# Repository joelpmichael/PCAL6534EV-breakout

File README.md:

# PCAL6534EV Breakout

## Contents

- [What?](#what)
- [Why?](#why)
- [How?](#how)
- [Can I buy one?](#can-i-buy-one)
- [Can I make one?](#can-i-make-one)
- [Can I make heaps and sell them?](#can-i-make-heaps-and-sell-them)
- [No really, why?](#no-really-why)
- [Board revision history](#board-revision-history)

## What?

This is a breakout board for the [NXP PCAL6534EV I2C GPIO expander](https://www.nxp.com/products/interfaces/ic-spi-i3c-interface-devices/general-purpose-i-o-gpio/ultra-low-voltage-level-translating-34-bit-ic-bus-smbus-i-o-expander:PCAL6534). The board breaks out 32 out of the possible 34 GPIO pins, with 26 of the 32 GPIO pins arranged in a DIP-style layout at 12.7mm column spacing which is perfect for breadboard or protoboard use. There is also a [SparkFun QWIIC-compatible connector](https://www.sparkfun.com/qwiic), for easy connection to other QWIIC-compatible boards.

## Why?

It all started a few years ago, when I was on a holiday in Italy and I found this wonderful little cafe that I stopped at for lunch. I convinced the chef to give me his secret recipe, which he did on one condition: I'm not allowed to tell anybody else until the day I die.

I'm still well and truly alive despite all reports to the contrary, and despite the lack of sleep (#DadLife), so I'm not going to tell you, instead I'm going to make this breakout board instead.

## How?

Please refer to the [PCAL6534EV Datasheet](https://www.nxp.com/docs/en/data-sheet/PCAL6534.pdf) and the [Board Schematic](PCAL6534EV-breakout.pdf) for further details.

- [Connecting](#connecting)
- [Powering](#powering)
- [I2C communication](#i2c-communication)
- [Interrupt and reset](#interrupt-and-reset)
- [GPIO use](#gpio-use)
- [Mounting](#mounting)

### Connecting

Solder the 20-pin headers into each side and slam it into a breadboard! The width is minimised to allow access to 3 pins on each side - wider breakout and prototype boards have always annoyed me by only allowing access to 1 or 2 pins on each side.

Use the QWIIC-compatible connector J1 to connect to your MCU, as the PCAL6534EV is optimised to run at 3.3V. You may run into current supply limits when using the very thin 28AWG wire in QWIIC-compatible cables, as the PCAL6534EV can source up to 450mA or sink up to 500mA of current. If you're driving a lot of LEDs or something, hook up an additional 3.3V power connection to the pin header, and maybe a chonky electrolytic capacitor across 3V3 or VIO.

You can also solder wires directly to the pin headers if needed, or solder the pin headers to a protoboard, or just do what you want I'm not your mum.

At the very bottom edge of the breakout board is an exposed ground plane, designed for you to attach an alligator clip while probing with a multimeter, osciloscope, or logic analyzer.

### Powering

The PCAL6534EV requires 2 power supplies, VDD(i2c) and VDD(p). VDD(i2c) is wired to the 3V3 rail, and must be in the range of 0.8 to 3.6V, allowing you to use lower voltage MCU or FPGA I2C lines. VDD(p) is wired to jumper JP1, and must be in the range of 1.65 to 5.5V. Jumper JP1 selects the source rail of VDD(p), either 3V3 or VIO. When jumper JP1 is set to 3V3, the 3V3 input voltage range is narrowed to 1.65 to 3.6V. When jumper JP1 is set to VIO, the desired IO voltage must be supplied on the VIO pin.

### I2C communication

The PCAL6534EV supports I2C standard-mode at up to 100kHz, fast-mode at up to 400kHz, or fast-mode plus at up to 1000kHz. The breakout board contains 4.7kΩ pull-up resistors from I2C SDA and SCL lines to the 3V3 rail. These pull-up resistors can be disabled by cutting the PCB trace jumper JP4 on the back of the breakout board.

The PCAL6534EV I2C device address is set by connecting the ADDR line to either SDA, SCL, VSS (ground), or VDD(i2c), with a base 7-bit I2C device address of `0b0100000` (`0x20`). The breakout board defaults to the base address `0x20`, and by cutting and bridging PCB jumper pins on JP2 and JP3 can set the device address to `0x20`, `0x21`, `0x22`, or `0x23` according to the following table:

|Jumper|Pins|Address|
|------|----|-------|
|JP2|1-2|0x20|
|JP2|2-3|0x21|
|JP3|1-2|0x22|
|JP3|2-3|0x23|

> ⚠️ SDA and SCL pins **ARE NOT** 5V-tolerant!

### Interrupt and reset

The PCAL6534EV contains both an Interrupt (IRQ) line, and a Reset (RST) line. Both lines are active-low. The IRQ output line uses an open-drain driver, and the breakout board contains a 10kΩ pull-up resistor to VDD(i2c) because most likely you'll be using the IRQ signal on the same MCU that the I2C controller is running on. If you really really really REALLY need to change this, you can remove R4 and connect another pull-up resistor between R4 pad 1 (closest to JP4) and VIO, ensuring that VIO is limited to 3.3V.

The Reset input line is an active-low input, and the breakout board contains a a 10kΩ pull-up resistor to VDD(i2c) because most likely you'll be supplying the Reset signal from the same MCU that the I2C controller is running on, or you've wired the Reset line to an external momentary switch and you don't care about the voltage. If you're using a momentary switch, add a 0.1µF capacitor in parallel to the switch for a hardware debouncer and noise filter. It is safe to leave the Reset line disconnected from the breakout board.

> ⚠️ Interrupt and Reset pins **ARE NOT** 5V-tolerant!

### GPIO use

It's a... uh... low-speed GPIO? Just use them, the default PCAL6534EV configuration should work for most cases! All the GPIO pins are 5V-tolerant, and will even produce 5V output if you're using 5V on VIO, so feel free to hook them up to your old MEGA328P-based Arduinos and do voltage level translation. You can even drive a LOT of LEDs directly from the GPIO pins - every pin is recommended to source 10mA or sink 25mA of current, with a combined total of 450mA of sourcing current and 500mA of sinking current.

For advanced use-cases, such as enabling internal 100kΩ pull-up or pull-down resistors, switching between push-pull or open-drain output mode, enabling interrupt generation, enabling debouncing filters, or reducing the drive strength to limit GPIO switching noise, please refer to the datasheet and the example source code.

> ✔️ GPIO pins **ARE** 5V-tolerant!

### Mounting

Due to asthetics and space constraints there isn't enough room for a full-size mounting hole, however in the middle of the OSHW logo there is a 1mm pilot hole that you can use to drill a mounting hole. Ideal? No. Pragmatic? Yes. 

Personally I wouldn't drill a hole larger than 3mm, which will allow you to use a M3 fastener, but you should be able drill up to a 5mm hole without hitting traces. If using metal fasteners, use nylon washers to avoid damage to traces by screw heads.

## Can I buy one?

Sure! Once I've got enough requests for a small batch run I'll send off an order. I test every single board to make sure it's fully functional before shipping.

## Can I make one?

Sure, why not? The board is designed to be manufactured using JLCPCB's 6-layer fabrication constraints as at March 2024 by using budget-size 50mm maximum dimension, budget 0.3mm drill size, 0.8mm thickness, 1oz outer copper, 0.5oz inner copper, and the budget (but surprisingly good) JLC06081H-1080A stackup. It currently does not meet OSHPARK fabrication constraints, as the trace and space minimum of 0.09mm is smaller than the required 0.1mm and there is some via-in-pad use which is currently unsupported.

## Can I make heaps and sell them?

Technically yes, but I'd love it if you gave me a cut in exchange for the testing system that I've developed.

## No really, why?

I wanted to use this GPIO expander in another project, and making a breakout board was probably the best way to verify if my layout hacks would work at all.

Also, shits and giggles: seeing who's both willing and able to manufacture the boards.

## Board Revision History

- [P1](#p1-prototype-1)

### P1: Prototype 1

First prototype, for testing if this even works at all

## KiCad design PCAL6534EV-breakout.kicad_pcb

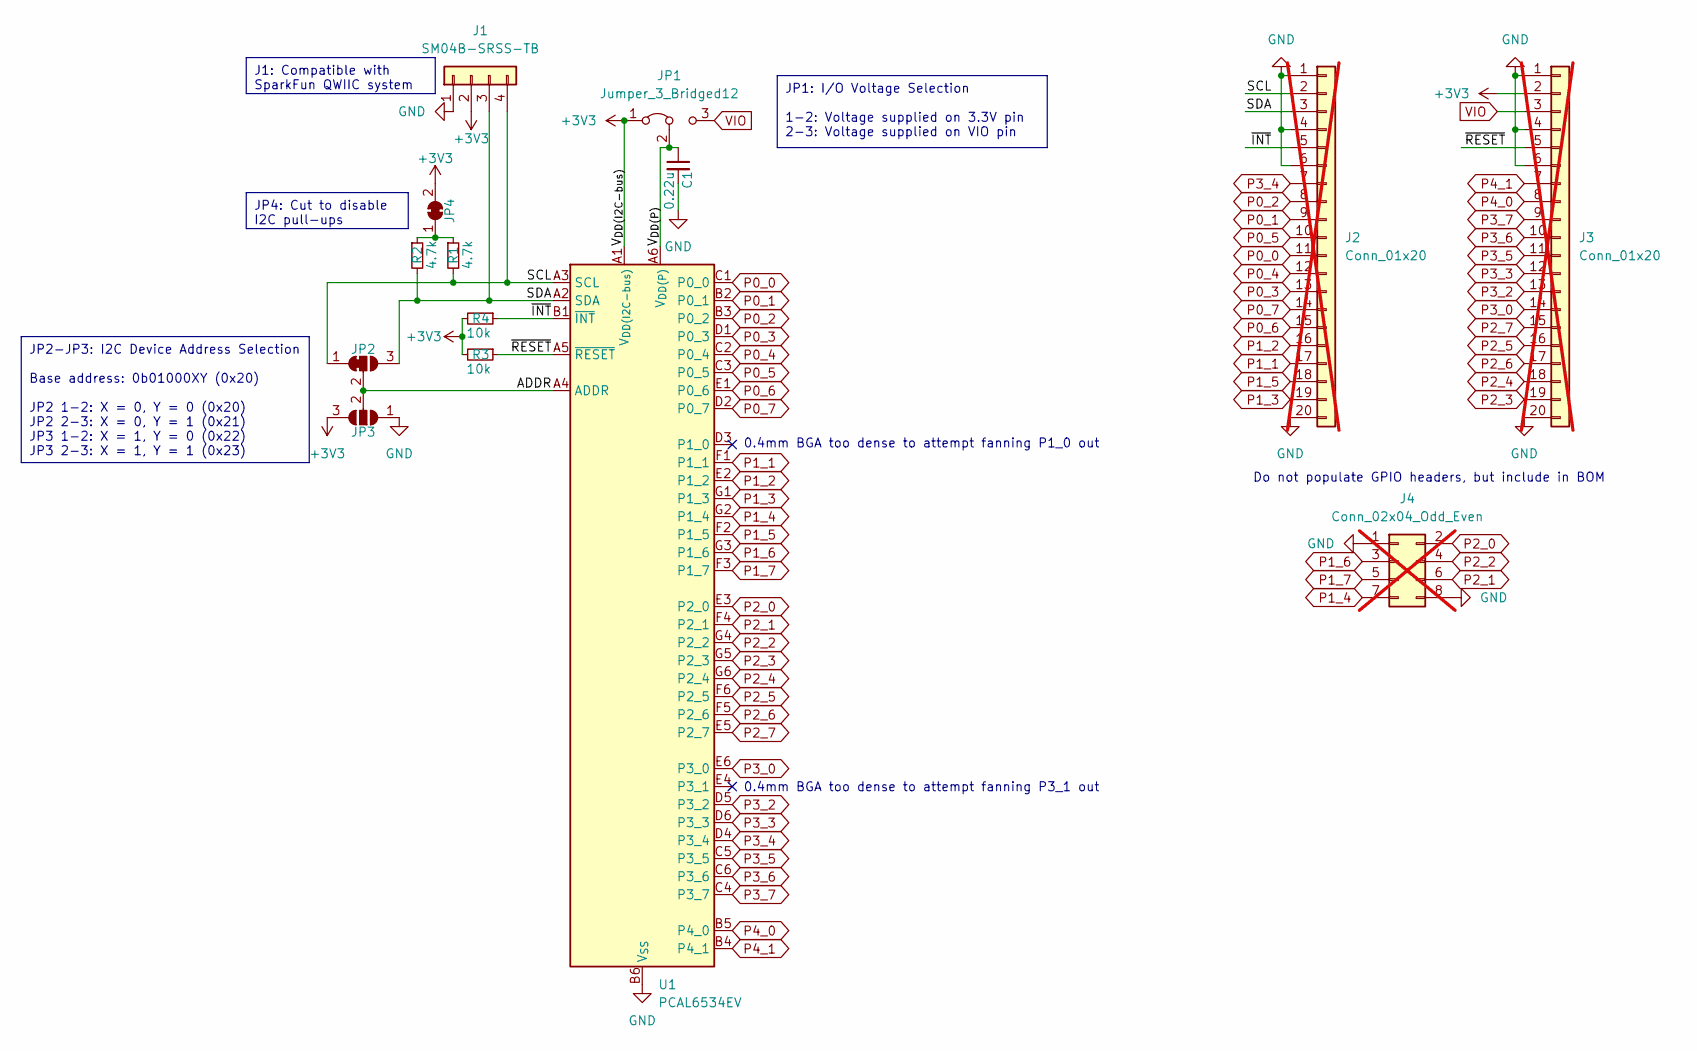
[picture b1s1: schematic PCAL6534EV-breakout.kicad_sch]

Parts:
C1: 0.22u; C_0402_1005Metric
J1: SM04B-SRSS-TB; JST_SH_SM04B-SRSS-TB_1x04-1MP_P1.00mm_Horizontal
J2, J3: Conn_01x20; PinHeader_1x20_P2.54mm_Vertical; not fitted
J4: Conn_02x04_Odd_Even; PinHeader_2x04_P2.54mm_Vertical; not fitted
JP1: Jumper_3_Bridged12; PinHeader_1x03_P2.54mm_Vertical
JP2: SolderJumper_3_Bridged12; SolderJumper-3_P1.3mm_Bridged12_RoundedPad1.0x1.5mm_NumberL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
JP3: SolderJumper_3_Open; SolderJumper-3_P1.3mm_Open_RoundedPad1.0x1.5mm_NumberLabels
JP4: SolderJumper_2_Bridged; SolderJumper-2_P1.3mm_Bridged_RoundedPad1.0x1.5mm
R1, R2: 4.7k; R_0402_1005Metric
R3, R4: 10k; R_0402_1005Metric
U1: PCAL6534EV; NXP_VFBGA-42_2.6x3mm_Layout6x7_P0.4mm_Ball0.25mm_Pad0.24mm

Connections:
+3V3: J1.2, J3.2, JP1.1 (A), JP3.3 (B), JP4.2 (B), R3.2, R4.2, U1.A1 (V_{DD(I2C-bus)})
/ADDR: JP2.2 (C), JP3.2 (C), U1.A4 (ADDR)
/SCL: J1.4, J2.2, JP2.1 (A), R1.2, U1.A3 (SCL)
/SDA: J1.3, J2.3, JP2.3 (B), R2.2, U1.A2 (SDA)
/V_{DD(P)}: C1.1, JP1.2 (C), U1.A6 (V_{DD(P)})
/~INT: J2.5, R4.1, U1.B1 (~INT)
/~RESET: J3.5, R3.1, U1.A5 (~RESET)
GND: C1.2, J1.1, J1.MP, J2.1, J2.4, J2.6, J2.20, J3.1, J3.4, J3.6, J3.20, J4.1, J4.8, JP3.1 (A), U1.B6 (V_{SS})
unnamed: JP4.1 (A), R1.1, R2.1
P0_0: J2.11, U1.C1 (P0_0)
P0_1: J2.9, U1.B2 (P0_1)
P0_2: J2.8, U1.B3 (P0_2)
P0_3: J2.13, U1.D1 (P0_3)
P0_4: J2.12, U1.C2 (P0_4)
P0_5: J2.10, U1.C3 (P0_5)
P0_6: J2.15, U1.E1 (P0_6)
P0_7: J2.14, U1.D2 (P0_7)
P1_1: J2.17, U1.F1 (P1_1)
P1_2: J2.16, U1.E2 (P1_2)
P1_3: J2.19, U1.G1 (P1_3)
P1_4: J4.7, U1.G2 (P1_4)
P1_5: J2.18, U1.F2 (P1_5)
P1_6: J4.3, U1.G3 (P1_6)
P1_7: J4.5, U1.F3 (P1_7)
P2_0: J4.2, U1.E3 (P2_0)
P2_1: J4.6, U1.F4 (P2_1)
P2_2: J4.4, U1.G4 (P2_2)
P2_3: J3.19, U1.G5 (P2_3)
P2_4: J3.18, U1.G6 (P2_4)
P2_5: J3.16, U1.F6 (P2_5)
P2_6: J3.17, U1.F5 (P2_6)
P2_7: J3.15, U1.E5 (P2_7)
P3_0: J3.14, U1.E6 (P3_0)
P3_2: J3.13, U1.D5 (P3_2)
P3_3: J3.12, U1.D6 (P3_3)
P3_4: J2.7, U1.D4 (P3_4)
P3_5: J3.11, U1.C5 (P3_5)
P3_6: J3.10, U1.C6 (P3_6)
P3_7: J3.9, U1.C4 (P3_7)
P4_0: J3.8, U1.B5 (P4_0)
P4_1: J3.7, U1.B4 (P4_1)
VIO: J3.3, JP1.3 (B)

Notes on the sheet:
JP1: I/O Voltage Selection 1-2: Voltage supplied on 3.3V pin 2-3: Voltage supplied on VIO pin
J1: Compatible with SparkFun QWIIC system
JP4: Cut to disable I2C pull-ups
JP2-JP3: I2C Device Address Selection Base address: 0b01000XY (0x20) JP2 1-2: X = 0, Y = 0 (0x20) JP2 2-3: X = 0, Y = 1 (0x21) JP3 1-2: X = 1, Y = 0 (0x22) JP3 2-3: X = 1, Y = 1 (0x23)
0.4mm BGA too dense to attempt fanning P3_1 out
Do not populate GPIO headers, but include in BOM
0.4mm BGA too dense to attempt fanning P1_0 out

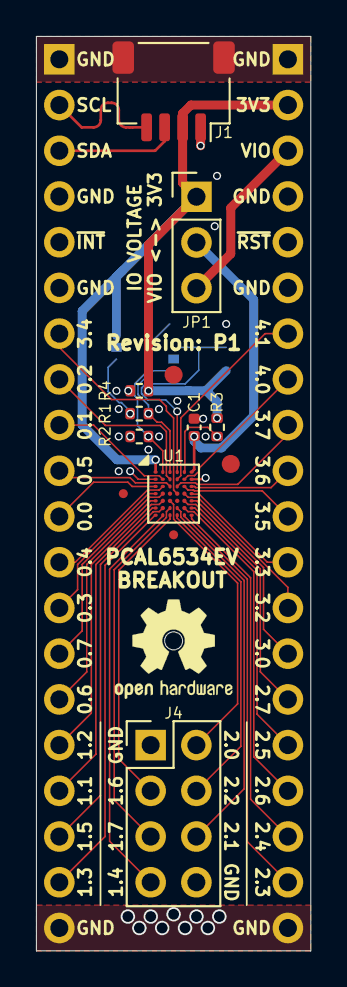
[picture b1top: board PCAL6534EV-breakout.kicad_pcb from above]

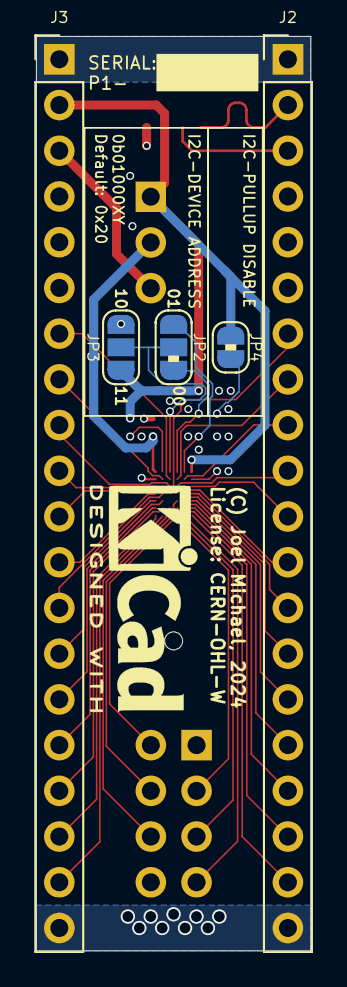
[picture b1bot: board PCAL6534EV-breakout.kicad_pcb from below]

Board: 6 copper layers, 15.2 x 50.8 mm, 18 parts (5 on the bottom side), 42 nets.

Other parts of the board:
FID1, FID2: Fiducial_0.5mm_Mask1mm
FID3, FID4: Fiducial_1mm_Mask2mm

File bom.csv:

"Reference","Value","Datasheet","Footprint","Qty","DNP"
"C1","0.22u","~","Capacitor_SMD:C_0402_1005Metric","1",""
"J1","SM04B-SRSS-TB","~","Connector_JST:JST_SH_SM04B-SRSS-TB_1x04-1MP_P1.00mm_Horizontal","1",""
"J2,J3","Conn_01x20","~","Connector_PinHeader_2.54mm:PinHeader_1x20_P2.54mm_Vertical","2","DNP"
"J4","Conn_02x04_Odd_Even","~","Connector_PinHeader_2.54mm:PinHeader_2x04_P2.54mm_Vertical","1","DNP"
"JP1","Jumper_3_Bridged12","~","Connector_PinHeader_2.54mm:PinHeader_1x03_P2.54mm_Vertical","1",""
"R1,R2","4.7k","~","Resistor_SMD:R_0402_1005Metric","2",""
"R3,R4","10k","~","Resistor_SMD:R_0402_1005Metric","2",""
"U1","PCAL6534EV","https://www.nxp.com/docs/en/data-sheet/PCAL6534.pdf","Package_BGA:NXP_VFBGA-42_2.6x3mm_Layout6x7_P0.4mm_Ball0.25mm_Pad0.24mm","1",""

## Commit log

2024-03-14 git gud
2024-03-14 add pdf of schematic
2024-03-14 choose your weapon (legal)
2024-03-14 add more art
2024-03-14 add renders
2024-03-14 prep outputs for manufacturing
2024-03-15 note to self: run DRC _BEFORE_ exporting
2024-03-15 initial checkin
2024-03-15 jit-hub-display-fixes
2024-03-15 add fiducials; add pilot hole for drilling a mounting hole
2024-03-15 nudge here, prod there, and pretty soon you've changed the entire thing
2024-03-15 just slam them all in an update again
2024-03-15 this looks fucken sick!
2024-03-17 nudge BGA tracks around by 0.01mm; length-match I2C SDA and SCL lines
2024-04-11 initial pieces for driver examples
2024-04-11 add changelog/devlog; minor readme updates

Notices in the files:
PCAL6534EV-breakout.kicad_pcb:
License: CERN-OHL-W
